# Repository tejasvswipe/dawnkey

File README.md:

# DAWNKEY — BLARE alarm clock

A custom BLARE alarm clock with a 12-key MX keypad, TFT display, DS3231 real-time clock, two-AA battery input and a distinctive printable case. The enclosure preview uses a black battery pod, dark display bezel and black **“for tejas”** lettering.
# gallery

## Deliverables

- **PCB source:** `PCB/DawnKey.kicad_pro`, routed `PCB/DawnKey.kicad_pcb`, placement-only backup, reproducible generator and the full BOM.
- **Fabrication:** `Production/Gerbers.zip` with copper, mask, silkscreen, board outline and separate plated/non-plated drill files; `Production/placements.csv` for assembly.
- **Enclosure:** OpenSCAD source, print-ready STLs and per-part/assembly STEP files under `CAD/`.
- **Firmware:** Arduino sketch and the key-by-key guide under `Firmware/`.
- **Build docs:** [power, wiring and button guide](Docs/Power_and_IO.md), [system block diagram](Docs/System_Architecture.png), sources, preview and preflight report.
 handoff, not a board ready to order or rely on as an alarm clock; complete full KiCad DRC, resolve the router discrepancy, inspect the boost layout and bench-test the assembled device first. The exact checks are in [`Production/Preflight.md`](Production/Preflight.md).

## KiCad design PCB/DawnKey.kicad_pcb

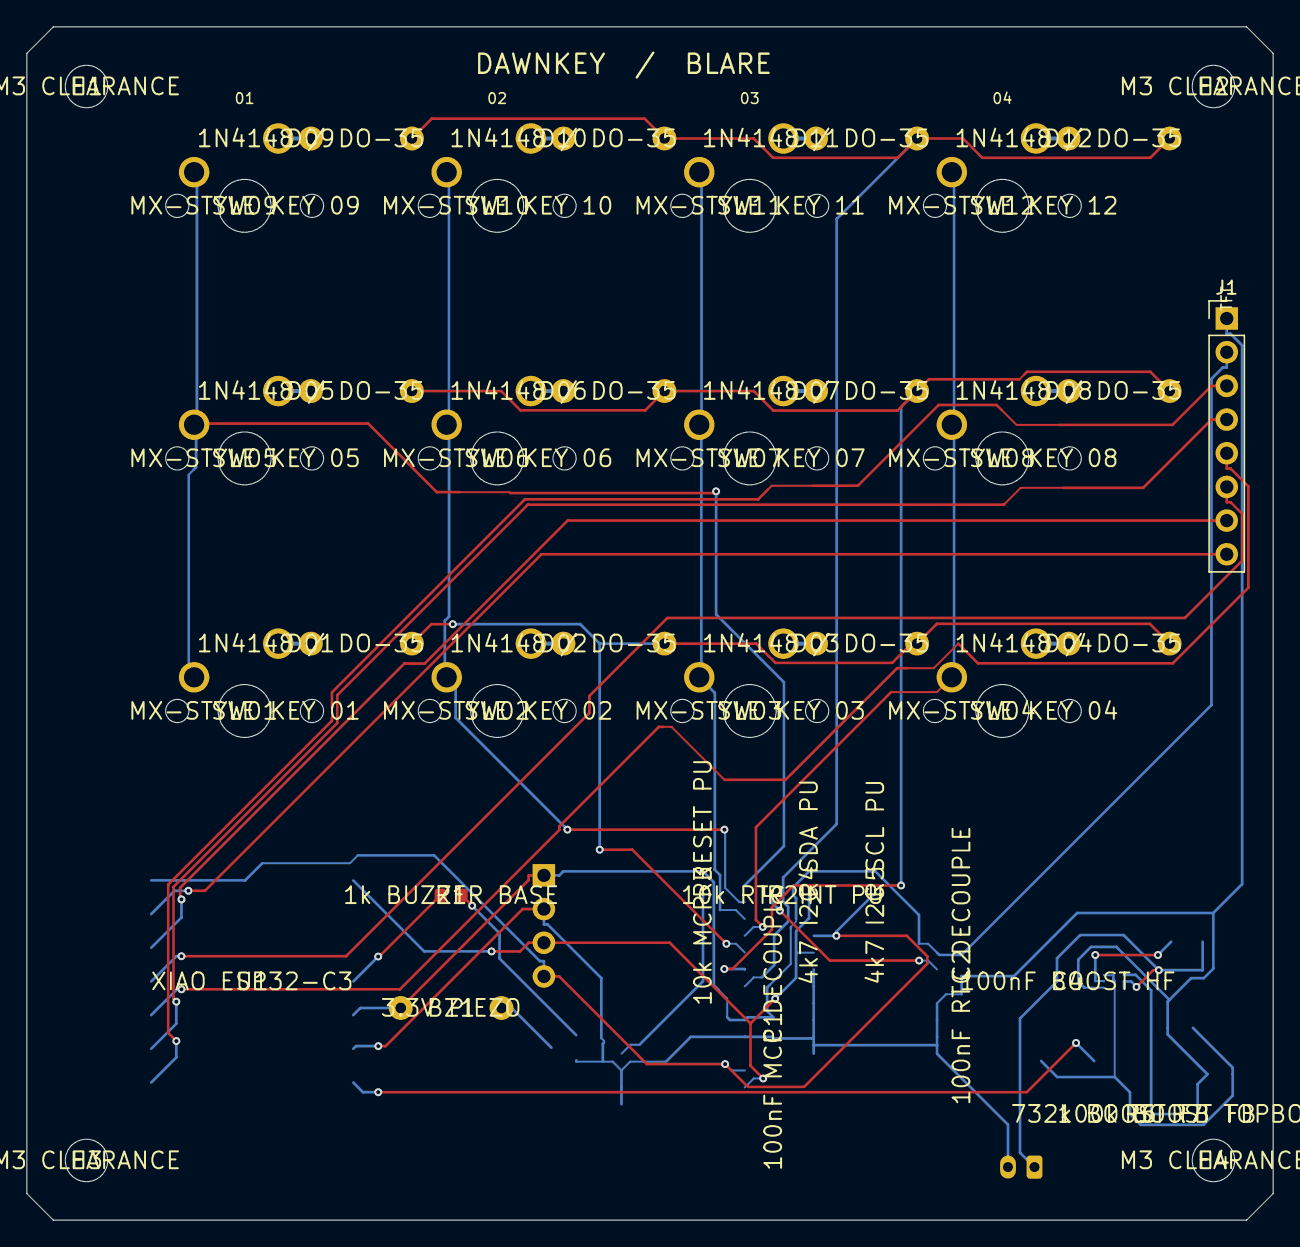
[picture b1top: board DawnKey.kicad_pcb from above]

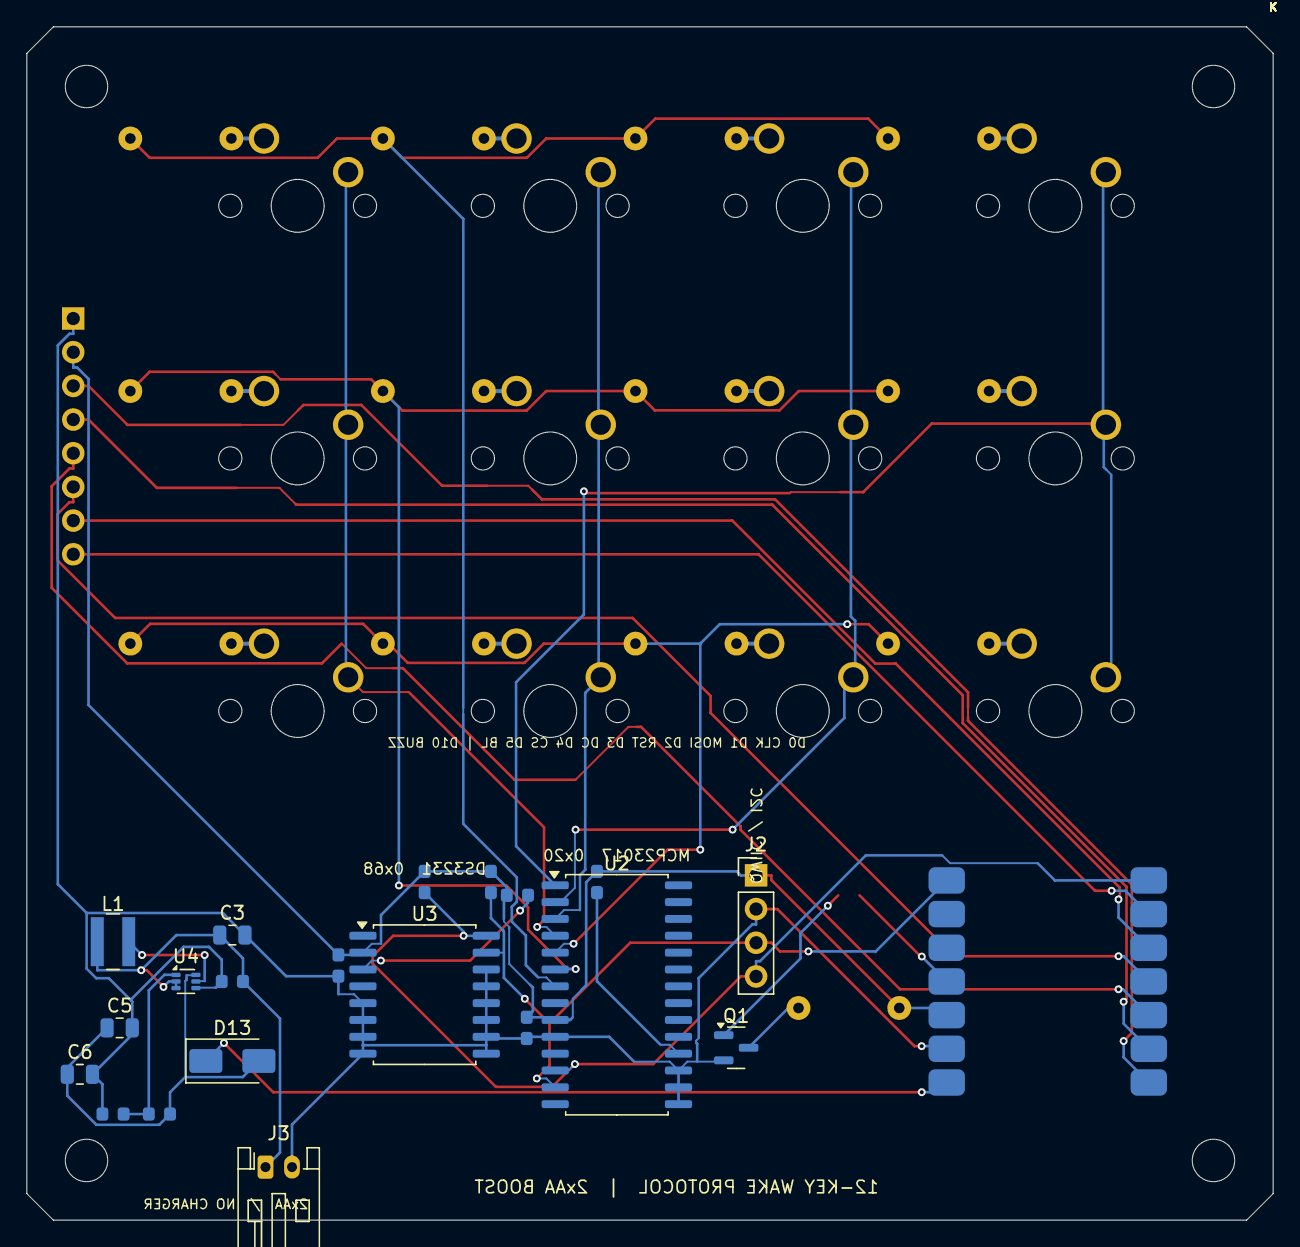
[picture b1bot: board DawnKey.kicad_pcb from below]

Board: 2 copper layers, 94.0 x 90.0 mm, 52 parts (34 on the bottom side), 39 nets.

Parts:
BZ1: 3.3V PIEZO; Buzzer_12x9.5RM7.6
C1: 100nF MCP DECOUPLE; C_0603_1608Metric
C2: 100nF RTC DECOUPLE; C_0603_1608Metric
C3: 10uF 10V X7R IN; C_0805_2012Metric
C4: 100nF BOOST HF; C_0603_1608Metric
C5, C6: 22uF 10V X7R OUT; C_0805_2012Metric
D01, D02, D03, D04, D05, D06, D07, D08, D09, D10, D11, D12: 1N4148 / DO-35; D_DO-35_SOD27_P7.62mm_Horizontal
D13: SS14 1A SCHOTTKY; D_SMA
H1, H2, H3, H4: M3 CLEARANCE; MountingHole_3.2mm_M3
J1: TFT / ST7789; PinHeader_1x08_P2.54mm_Vertical
J2: I2C EXPANSION: 3V3 GND SDA SCL; PinHeader_1x04_P2.54mm_Vertical
J3: 2xAA PACK (SWITCHED); JST_PH_S2B-PH-K_1x02_P2.00mm_Horizontal
L1: 1uH Isat>=7A; L_Wuerth_MAPI-4030
Q1: MMBT3904 / NPN; SOT-23
R1: 1k BUZZER BASE; R_0603_1608Metric
R2: 10k RTC INT PU; R_0603_1608Metric
R3: 10k MCP RESET PU; R_0603_1608Metric
R4: 4k7 I2C SDA PU; R_0603_1608Metric
R5: 4k7 I2C SCL PU; R_0603_1608Metric
R6: 732k BOOST FB TOP; R_0603_1608Metric
R7: 100k BOOST FB BOT; R_0603_1608Metric
SW01: MX-STYLE KEY 01; SW_MX_1u
SW02: MX-STYLE KEY 02; SW_MX_1u
SW03: MX-STYLE KEY 03; SW_MX_1u
SW04: MX-STYLE KEY 04; SW_MX_1u
SW05: MX-STYLE KEY 05; SW_MX_1u
SW06: MX-STYLE KEY 06; SW_MX_1u
SW07: MX-STYLE KEY 07; SW_MX_1u
SW08: MX-STYLE KEY 08; SW_MX_1u
SW09: MX-STYLE KEY 09; SW_MX_1u
SW10: MX-STYLE KEY 10; SW_MX_1u
SW11: MX-STYLE KEY 11; SW_MX_1u
SW12: MX-STYLE KEY 12; SW_MX_1u
U1: XIAO ESP32-C3; XIAO-ESP32-C3-SMD
U2: MCP23017-I/SO; SOIC-28W_7.5x17.9mm_P1.27mm
U3: DS3231S RTC; SOIC-16W_7.5x10.3mm_P1.27mm
U4: TPS61023 2xAA BOOST; SOT-563

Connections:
3V3: BZ1.1, C1.1, C2.1, J1.2, J2.1, R2.2, R3.1, R4.1, R5.1, U1.12, U2.9, U3.2
BAT_RAW: C3.1, C4.1, J3.1, L1.1, U4.2, U4.3
BOOST_5V: C5.1, C6.1, D13.2, R6.1, U4.6
BOOST_FB: R6.2, R7.1, U4.1
BOOST_SW: L1.2, U4.5
BUZZER: BZ1.2, Q1.3
BUZZER_CTL: R1.1, U1.11
BUZZER_SW: Q1.1, R1.2
GND: C1.2, C2.2, C3.2, C4.2, C5.2, C6.2, J1.1, J2.2, J3.2, Q1.2, R7.2, U1.13, U2.10, U2.15, U2.16, U2.17, U3.5, U3.6, U3.7, U3.8, U3.9, U3.10, U3.11, U3.12, U3.13, U3.14, U4.4
I2C_SCL: J2.4, R5.2, U1.7, U2.12, U3.16
I2C_SDA: J2.3, R4.2, U1.8, U2.13, U3.15
KEY_COL0: SW01.1, SW05.1, SW09.1, U2.1
KEY_COL1: SW02.1, SW06.1, SW10.1, U2.2
KEY_COL2: SW03.1, SW07.1, SW11.1, U2.3
KEY_COL3: SW04.1, SW08.1, SW12.1, U2.4
KEY_ROW0: D01.2, D02.2, D03.2, D04.2, U2.5
KEY_ROW1: D05.2, D06.2, D07.2, D08.2, U2.6
KEY_ROW2: D09.2, D10.2, D11.2, D12.2, U2.7
KINT01: D01.1, SW01.2
KINT02: D02.1, SW02.2
KINT03: D03.1, SW03.2
KINT04: D04.1, SW04.2
KINT05: D05.1, SW05.2
KINT06: D06.1, SW06.2
KINT07: D07.1, SW07.2
KINT08: D08.1, SW08.2
KINT09: D09.1, SW09.2
KINT10: D10.1, SW10.2
KINT11: D11.1, SW11.2
KINT12: D12.1, SW12.2
MCP_RESET: R3.2, U2.18
RTC_INT: R2.1, U3.3
TFT_BL: J1.8, U1.6
TFT_CS: J1.7, U1.5
TFT_DC: J1.6, U1.4
TFT_MOSI: J1.4, U1.2
TFT_RST: J1.5, U1.3
TFT_SCLK: J1.3, U1.1
USB_5V: D13.1, U1.14

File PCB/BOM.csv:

Reference,Qty,Description,Recommended part/value,Package / interface,Notes
U1,1,MCU module,Seeed XIAO ESP32-C3,Module,Kit part; mount on underside per board footprint
U2,1,I2C GPIO expander,MCP23017-I/SO,SOIC-28W,Address 0x20; keypad matrix
U3,1,RTC,DS3231S,SOIC-16W,Address 0x68; unused VBAT tied to GND
U4,1,AA boost converter,TI TPS61023DRLR or equivalent TPS61023 SOT-563,6-pin SOT-563,Check exact package variant/pin-1 mark against datasheet
L1,1,Boost inductor,Würth 74438357010 1uH,4.1x4.1mm shielded,Select >=7A saturation current; follow TI layout guidance
D13,1,5V isolation diode,SS14 Schottky,DO-214AC / SMA,Pad 2 anode=boost; pad 1 cathode=XIAO 5V
C3,1,Boost input capacitor,10uF 10V X7R,0805,Place tight to U4 VIN/GND
C4,1,High-frequency input bypass,100nF X7R,0603,Place tight to U4 VIN/GND
C5-C6,2,Boost output capacitors,22uF 10V X7R,0805,Parallel; check effective capacitance under DC bias
R6,1,Feedback upper resistor,732k 1%,0603,BOOST_5V to FB
R7,1,Feedback lower resistor,100k 1%,0603,FB to GND
DISP1,1,Display module,2.25in ST7789 76x284 panel,8-pin jumper cable,Kit item; VCC=3V3; BL active-low
J1,1,TFT connector,1x8 2.54mm pin header,Through-hole,BLARE kit order: GND,3V3,SCLK,MOSI,RST,DC,CS,BL
J2,1,I2C expansion,1x4 2.54mm header,Through-hole,3V3/GND/SDA/SCL
J3,1,2-cell battery input,JST-PH 2-pin 2.0mm,Side-entry connector,Two AA in series; switched battery-positive input
BT1,1,AA holder,2-cell AA series holder with JST-PH lead,External case pocket,Alkaline or NiMH pair; no charging circuit on PCB
SW-PWR,1,Power switch,SPST slide switch rated >=1A,Inline on AA positive lead,Panel slot in battery pod; confirm switch body dimensions
SW01-SW12,12,MX-style mechanical switches,BLARE kit switches,Plate-mount,4 columns x 3 rows; 19.05mm pitch
D01-D12,12,Signal diodes,1N4148,DO-35 axial,One per key; matrix direction per PCB
BZ1,1,Piezo buzzer,3.3V piezo,12mm / 7.6mm lead pitch,Kit item; driven by Q1
Q1,1,Buzzer NPN transistor,MMBT3904, SOT-23,Low-side switch; confirm package pinout
R1,1,Buzzer base resistor,1k,0603,GPIO-to-base
R2,1,RTC interrupt pull-up,10k,0603,RTC_INT net currently unused by starter code
R3,1,MCP reset pull-up,10k,0603,RESET to 3V3
R4-R5,2,I2C pull-ups,4.7k,0603,SDA and SCL to 3V3
C1-C2,2,Logic decoupling,100nF X7R,0603,One each for MCP23017 and DS3231
H1-H4,4,PCB mounting holes,M3 clearance,3.2mm NPTH,Match case supports/heat-set inserts
CASE,1,Enclosure set,Top plate, bottom shell, display bezel, battery pod and door,3D printed,See CAD folder; verify exact display/holder and switch sizes before printing

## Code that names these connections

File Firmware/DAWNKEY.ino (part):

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#include <Preferences.h>

// BLARE firmware guide pin assignments for the display.
#define TFT_SCLK 0
#define TFT_MOSI 1
#define TFT_RST  2
#define TFT_DC   3
#define TFT_CS   4
#define TFT_BL   5
// Main PCB routes the transistor buzzer control to XIAO D10 (GPIO10),
// deliberately avoiding the GPIO8/GPIO9 boot-strapping pins.
#define BUZZER_PIN D10
// I2C uses the XIAO pads routed to D7 (SDA) and D6 (SCL), not the TFT pins.
#define I2C_SDA_PIN D7
#define I2C_SCL_PIN D6

class DawnKeyST7789 : public Adafruit_ST7789 {
 public:
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}

void stopAlarm() {
  noTone(BUZZER_PIN);
  mode = NORMAL;
  snoozeArmed = false;
  alarmCode = "";
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}

void enterSetMode(UiMode target) {
  noTone(BUZZER_PIN);
  digits = "";
  mode = target;
  drawUi();
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
  if (key == 10) {  // Button 11: SNOOZE / CLOCK SET
    if (mode == RINGING) {
      noTone(BUZZER_PIN);
      mode = NORMAL;
      snoozeArmed = true;
      snoozeAt = rtc.now().unixtime() + SNOOZE_SECONDS;
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
void setup() {
  Serial.begin(115200);
  pinMode(TFT_BL, OUTPUT);
  digitalWrite(TFT_BL, LOW);  // BLARE TFT backlight is active-low.
  pinMode(BUZZER_PIN, OUTPUT);
  noTone(BUZZER_PIN);

  Wire.begin(I2C_SDA_PIN, I2C_SCL_PIN);
  if (!mcp.begin_I2C(MCP_ADDR, &Wire)) {
    Serial.println("ERROR: MCP23017 not found at 0x20");
  } else {
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  if (mode == RINGING && now - lastBeep >= 550) {
    lastBeep = now;
    beepPhase = !beepPhase;
    tone(BUZZER_PIN, beepPhase ? 2200 : 1650);
  }
  if (mode == NORMAL && now - lastUiDraw >= 1000) {
    lastUiDraw = now;
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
